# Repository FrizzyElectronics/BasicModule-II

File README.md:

# BasicModule-II
This is the second basic module that we created. As the first one, this board was designed to hold different components in order to lower the cost of manufacturing. This board can carry a bush button, an end-stop sensor, or a photosensor (LDR).

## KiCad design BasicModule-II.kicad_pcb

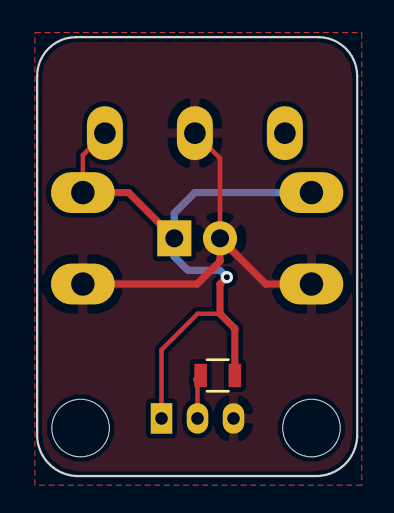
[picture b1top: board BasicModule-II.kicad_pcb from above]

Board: 2 copper layers, 17.8 x 24.4 mm, 5 parts (0 on the bottom side), 3 nets.

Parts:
P1: CONN_01X03; JST_PH_S3B-PH-K_03x2.00mm_Angled
R1: 10k; R_0805
R2: R_PHOTO; LED-5MM
SW1: Pulsador; SW_PUSH-12mm
SW2: Final_carrera; limit_sw_tiaihua

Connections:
5V: P1.2, R1.1
GND: P1.3, R2.2, SW1.2, SW2.3
SIGNAL: P1.1, R1.2, R2.1, SW1.1, SW2.2

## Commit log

2017-05-08 License Added
2017-05-08 Esquema empezado y plantilla de pcb añadida
2017-05-14 ERC pasado, esquema terminado
2017-05-14 LAyout terminado
2017-05-14 Serigrafia añadida
2017-06-26 Error del final de carrera subsanado
2018-01-20 Gerbers exportados
    Gerbers exportados para prueba de panelizacion
2018-02-05 Logo atomo añadido
2018-02-10 Conector cambiado
2018-02-24 Logo girado
2018-03-03 Actualizacion del arbol de carpetas
2018-03-11 Updated module description
2018-05-06 BOM exportado
2018-05-06 gerbers generados
2018-07-14 Re-rellenado el plano de masa
2018-07-15 Gerbers exportados
